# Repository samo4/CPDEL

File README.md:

# CPDEL

## Completely Pointless DC Electronic Load

> This a 2-channel DC electronic load, built from [cheap chinese DC load modbus modules](./firmware/SOUSIM.md).

Features:

- 2 channels: 200V, 10A
- 4 modes (CC, CV, CR, CP) + battery discharge mode
- Control:
  - 2.8" SPI display with capacitive touch
  - telnet SCPI interface (port 5025)
  - REST SCPI interface (port 80)
  - responsive web interface (with sockets)
- rudimentary charting
- OTA updates with CI/CD integration
- not-unreasonable level of test coverage
- UDP logging for debugging

## Development

You need a working installation of Python 3.x, [ESP-IDF v6.x](https://docs.espressif.com/projects/esp-idf/en/stable/esp32/get-started/windows-setup.html) and a working C compiler (the Xtensa one and a native for your host system - tested only with Visual studio build system). Use vscode to open the firmware folder, which contains the `.vscode` settings, including the most important: initialization of ESP-IDF terminal.

In ESP-IDF terminal (folder `firmware/esp`) you can then run `./esp.ps1`

## Key takeaways

- don't use http servers for OTA that you don't fully control, because you have no control over TLS chain.. updates to chain can break your OTA
- don't use SPI display if you want full screen animations, it's too slow
- don't use single pole switches for mains...
- keep LVGL memory as low as possible, to crash early when we have a leak?

## LLM disclaimer

Hardware and first few versions of software were created the old fashined way. It worked, but only the exact features that I needed at the time. With the help of LLM, the code was rewritten to use ESP-IDF (compared to original Arduino FreeRTOSnstein) directly and implement basicly all of the features that one might expect from a DC load instrument. LLM was used heavily especially in the UI, http/ws/socket server code and test writing.

"Copilot Is For Entertainment Purposes Only" is written in the Copilot terms. Well, I was entertained.

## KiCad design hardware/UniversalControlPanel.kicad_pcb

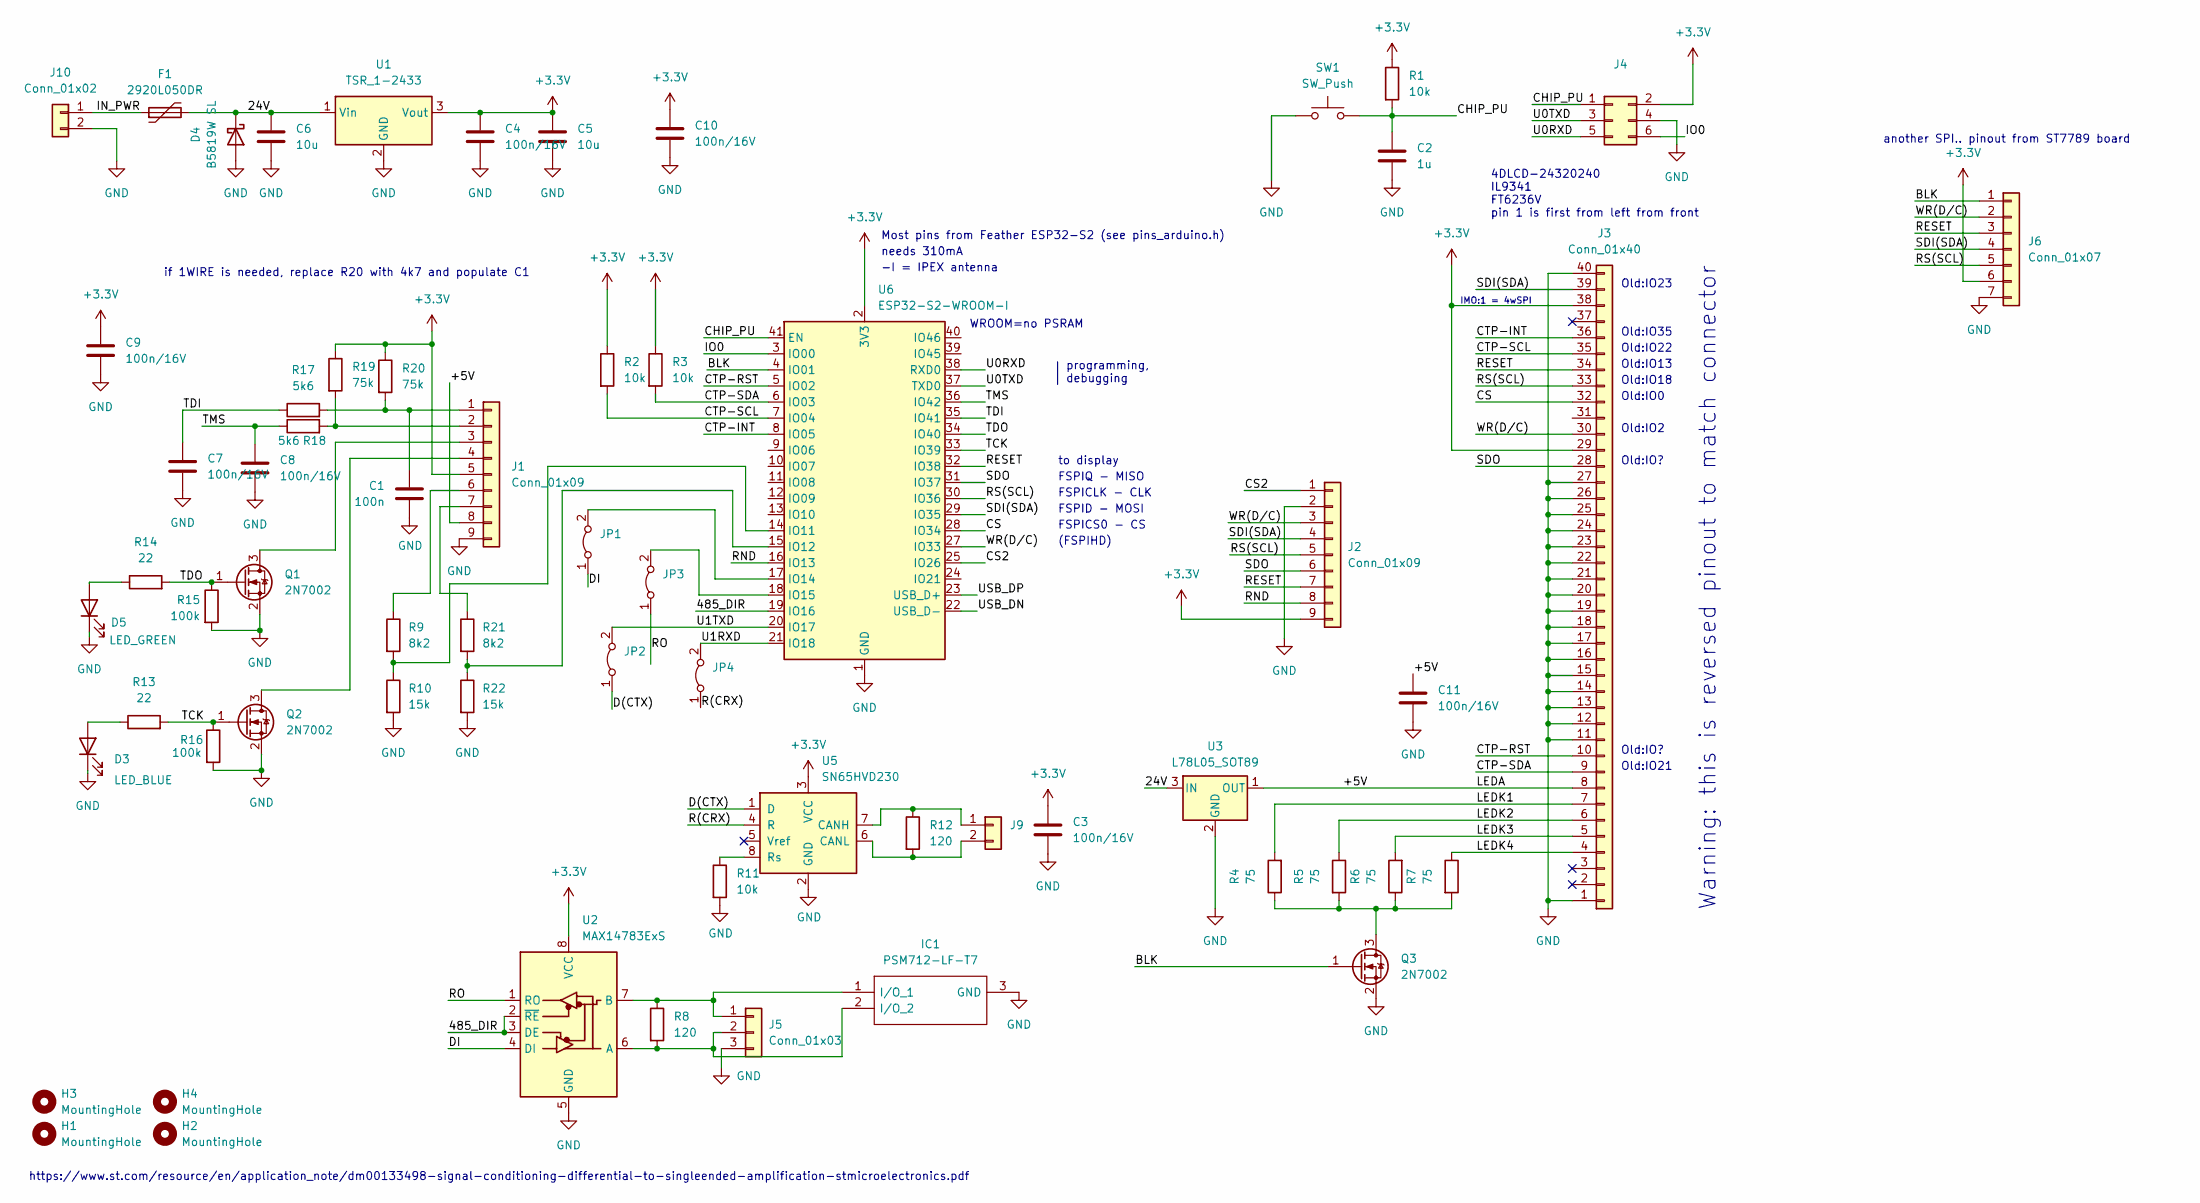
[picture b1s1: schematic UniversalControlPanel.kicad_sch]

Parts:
C1: 100n; C_0402_1005Metric; LCSC C1525
C2: 1u; C_0402_1005Metric
C3, C4, C7, C8, C9, C10, C11: 100n/16V; C_0402_1005Metric; LCSC C1525
C5, C6: 10u; C_1206_3216Metric; LCSC C13585
D3: LED_BLUE; LED_0603_1608Metric; LCSC C72041
D4: B5819W SL; D_SOD-123; LCSC C8598
D5: LED_GREEN; LED_0603_1608Metric; LCSC C72043
F1: 2920L050DR; Fuse_2920_7451Metric; Mouser Part Number 576-2920L050
H1, H2, H3, H4: MountingHole; MountingHole_3.5mm
IC1: PSM712-LF-T7; SOT-23; Manufacturer_Part_Number PSM712-LF-T7; LCSC C32677
J1: Conn_01x09; JST_XH_B9B-XH-A_1x09_P2.50mm_Vertical
J2: Conn_01x09; PinHeader_1x09_P2.54mm_Vertical
J3: Conn_01x40; Hirose_FH12-40S-0.5SH_1x40-1MP_P0.50mm_Horizontal; LCSC C506795
J4: Conn_02x03_Odd_Even; PinHeader_2x03_P2.54mm_Vertical
J5: Conn_01x03; JST_XH_B3B-XH-A_1x03_P2.50mm_Vertical
J6: Conn_01x07; PinHeader_1x07_P2.54mm_Vertical
J9: Conn_01x02; JST_XH_B2B-XH-A_1x02_P2.50mm_Vertical
J10: Conn_01x02; 1985807
JP1, JP2, JP3, JP4: Jumper_2_Bridged; SolderJumper-2_P1.3mm_Bridged2Bar_RoundedPad1.0x1.5mm
Q1, Q2, Q3: 2N7002; SOT-23; LCSC C8545
R1, R2, R3, R11: 10k; R_0402_1005Metric; LCSC C25744
R4, R5, R6, R7: 75; R_0402_1005Metric; LCSC C25133
R8, R12: 120; R_0805_2012Metric_Pad1.20x1.40mm_HandSolder
R9, R21: 8k2; R_0402_1005Metric; LCSC C25924
R10, R22: 15k; R_0402_1005Metric; LCSC C25756
R13, R14: 22; R_0402_1005Metric
R15, R16: 100k; R_0402_1005Metric
R17, R18: 5k6; R_0402_1005Metric; LCSC C25908
R19, R20: 75k; R_0402_1005Metric; LCSC C25798
SW1: SW_Push; TS-1187A-B-A-B; LCSC C318884
U1: TSR_1-2433; Converter_DCDC_TRACO_TSR-1_THT
U2: MAX14783ExS; SOIC-8_3.9x4.9mm_P1.27mm; LCSC C559550
U3: L78L05_SOT89; SOT-89-3
U5: SN65HVD230; SOIC-8_3.9x4.9mm_P1.27mm
U6: ESP32-S2-WROOM-I; ESP32-S2-WROVER; LCSC C967026

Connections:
+3V3: C3.1, C4.1, C5.1, C9.1, C10.1, J1.5, J2.9, J3.29, J3.38, J4.2, J6.6, R1.1, R2.1, R3.1, R19.1, R20.1, U1.3 (Vout), U2.8 (VCC), U5.3 (VCC), U6.2 (3V3)
/24V: C6.1, D4.1 (K), F1.2, U1.1 (Vin), U3.3 (IN)
/485_DIR: U2.2 (~RE), U2.3 (DE), U6.19 (IO16)
/+5V: C11.1, J1.8, J3.8, U3.1 (OUT)
/BLK: J6.1, Q3.1 (G), U6.4 (IO01)
/CHIP_PU: C2.1, J4.1, R1.2, SW1.2, U6.41 (EN)
/CS: J3.32, U6.28 (IO34)
/CS2: J2.1, U6.25 (IO26)
/CTP-INT: J3.36, U6.8 (IO05)
/CTP-RST: J3.10, U6.5 (IO02)
/CTP-SCL: J3.35, R2.2, U6.7 (IO04)
/CTP-SDA: J3.9, R3.2, U6.6 (IO03)
/D(CTX): JP2.1 (A), U5.1 (D)
/DI: JP1.1 (A), U2.4 (DI)
/IN_PWR: F1.1, J10.1
/IO0: J4.6, U6.3 (IO00)
/LEDK1: J3.7, R4.2
/LEDK2: J3.6, R5.1
/LEDK3: J3.5, R6.2
/LEDK4: J3.4, R7.1
/R(CRX): JP4.1 (A), U5.4 (R)
/RESET: J2.7, J3.34, J6.3, U6.32 (IO38)
/RND: J2.8, U6.16 (IO13)
/RO: JP3.1 (A), U2.1 (RO)
/RS(SCL): J2.5, J3.33, J6.5, U6.30 (IO36)
/SDI(SDA): J2.4, J3.39, J6.4, U6.29 (IO35)
/SDO: J2.6, J3.28, U6.31 (IO37)
/TCK: Q2.1 (G), R13.2, R16.1, U6.33 (IO39)
/TDI: C7.1, R17.1, U6.35 (IO41)
/TDO: Q1.1 (G), R14.2, R15.1, U6.34 (IO40)
/TMS: C8.1, R18.1, U6.36 (IO42)
/U0RXD: J4.5, U6.38 (RXD0)
/U0TXD: J4.3, U6.37 (TXD0)
/U1RXD: JP4.2 (B), U6.21 (IO18)
/U1TXD: JP2.2 (B), U6.20 (IO17)
/USB_DN: U6.22 (USB_D-)
/USB_DP: U6.23 (USB_D+)
/WR(D/C): J2.3, J3.30, J6.2, U6.27 (IO33)
GND: C1.1, C2.2, C3.2, C4.2, C5.2, C6.2, C7.2, C8.2, C9.2, C10.2, C11.2, D3.1 (K), D4.2 (A), D5.1 (K), IC1.3 (GND), J1.9, J2.2, J3.1, J3.11, J3.12, J3.13, J3.14, J3.15, J3.16, J3.17, J3.18, J3.19, J3.20, J3.21, J3.22, J3.23, J3.24, J3.25, J3.26, J3.27, J3.40, J4.4, J5.3, J6.7, J10.2, Q1.2 (S), Q2.2 (S), Q3.2 (S), R10.2, R11.2, R15.2, R16.2, R22.2, SW1.1, U1.2 (GND), U2.5 (GND), U3.2 (GND), U5.2 (GND), U6.1 (GND), U6.26 (GND), U6.42 (GND), U6.43 (GND)
unnamed: C1.2, J1.1, R17.2, R20.2
unnamed: D3.2 (A), R13.1
unnamed: D5.2 (A), R14.1
unnamed: IC1.1 (I/O_1), J5.1, R8.1, U2.7 (B)
unnamed: IC1.2 (I/O_2), J5.2, R8.2, U2.6 (A)
unnamed: J1.2, R18.2, R19.2
unnamed: J1.3, Q1.3 (D)
unnamed: J1.4, Q2.3 (D)
unnamed: J1.6, R9.1
unnamed: J1.7, R21.1
unnamed: J9.1, R12.1, U5.7 (CANH)
unnamed: J9.2, R12.2, U5.6 (CANL)
unnamed: JP1.2 (B), U6.17 (IO14)
unnamed: JP3.2 (B), U6.18 (IO15)
unnamed: Q3.3 (D), R4.1, R5.2, R6.1, R7.2
unnamed: R9.2, R10.1, U6.14 (IO11)
unnamed: R11.1, U5.8 (Rs)
unnamed: R21.2, R22.1, U6.15 (IO12)

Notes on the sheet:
Old:IO35
Most pins from Feather ESP32-S2 (see pins_arduino.h)
Old:IO?
FSPICS0 - CS
Old:IO13
Old:IO23
WROOM=no PSRAM
(FSPIHD)
Warning: this is reversed pinout to match connector
-I = IPEX antenna
if 1WIRE is needed, replace R20 with 4k7 and populate C1
https://www.st.com/resource/en/application_note/dm00133498-signal-conditioning-differential-to-singleended-amplification-stmicroelectronics.pdf
Old:IO2
to display
IMO:1 = 4wSPI
FSPICLK - CLK
Old:IO22
Old:IO21
4DLCD-24320240 IL9341 FT6236V pin 1 is first from left from front
another SPI.. pinout from ST7789 board
FSPID - MOSI
FSPIQ - MISO
Old:IO18
needs 310mA
Old:IO0
programming, debugging

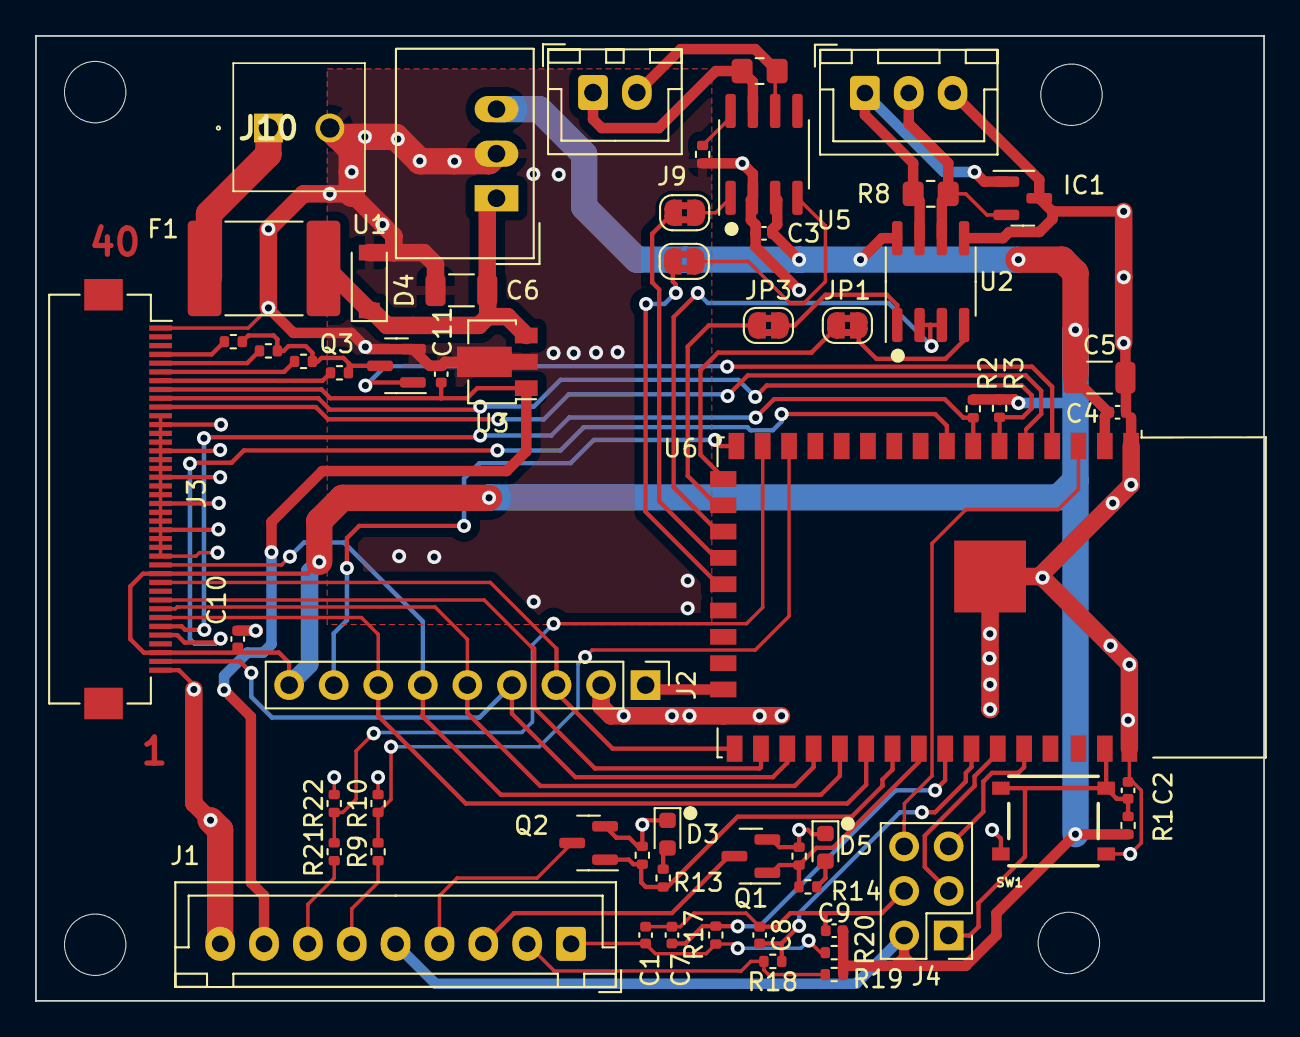
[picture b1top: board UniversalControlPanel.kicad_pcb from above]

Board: 2 copper layers, 70.0 x 55.0 mm, 62 parts (0 on the bottom side), 55 nets.

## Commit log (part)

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2022-01-02 initial
2022-01-02 components
2022-01-03 pcb first place
2022-01-03 removed autosave
2022-01-03 moved input sch
2022-01-03 some changes
2022-01-05 replaced with TSR
2022-01-05 hirose
2022-01-05 random additions
2022-01-06 finalizing features
2022-01-07 connector finalized
2022-01-07 placed
2022-01-09 movin st7789
2022-01-09 added switch
2022-07-24 restart work
2022-07-24 wired
2022-07-25 before reversing display
2022-07-25 before upload
2022-07-25 went to production
2023-03-05 joining
2024-10-26 failed experiment
2024-10-26 ipv6 says hello
2024-10-26 failing http ivp6
2024-10-27 panda
2024-11-03 ping package
2025-05-18 empty project
2025-05-18 more default
2025-05-18 default lv_conf
2025-05-18 my lv_conf
2025-05-18 old lv_conf
2025-05-20 why this compiles?
2025-05-27 smth
2026-03-20 playing
2026-03-20 compiles
2026-03-20 it's something
2026-03-21 nice numpad
2026-03-21 worky
2026-03-21 first graph
2026-03-21 wireless mockup
2026-03-21 less rounded corners
2026-03-21 wifi config
2026-03-22 esp ifdef
2026-03-22 more reliable cmake
2026-03-22 stack checking and null ptr
2026-03-22 defensive prog
2026-03-22 split folders
2026-03-22 tidy
2026-03-22 esp ignore
2026-03-22 lv_conf_common
2026-03-22 esp builds
2026-03-22 safe
2026-03-22 display no-worky
2026-03-22 ILI9341 build. works? who knows
2026-03-22 moved mains
2026-03-22 ready for OTA
2026-03-23 spi works
2026-03-23 ili9341_init_from_datasheet
2026-03-23 works
2026-03-23 straightforward build script
2026-03-24 touch in progress
2026-03-25 touch works
2026-03-25 faster link
2026-03-25 wifi works
2026-03-25 web server
2026-03-25 readme
2026-03-27 no anim, ch count, modal panel
2026-03-27 lv_obj_is_valid is not need if no free; no anim
2026-03-27 ch count
2026-03-27 ch count & is valid not needed
2026-03-27 add access to ssid/pass
2026-03-27 now with keyboard
2026-03-27 no more panice
2026-03-27 modbus wip
2026-03-27 going the queue dir
2026-03-28 already cute
2026-03-28 now with low_voltage_cutoff
2026-03-28 colors
2026-03-28 now with a nice unified struct for bus
2026-03-28 rename
2026-03-28 wrapping renaming
2026-03-28 hahahah
2026-03-28 Fix ESP-IDF setup and build steps
2026-03-28 Remove pkg_resources check in OTA workflow
2026-03-28 Fix CI app binary detection for ESP-IDF build output
2026-03-28 Simplify firmware binary detection (remove inline Python)
2026-03-28 OTA missing file
2026-03-29 ota ok
2026-03-29 modal, unused timer and ui_log
2026-03-29 ui_modal
2026-03-29 ui_log
2026-03-29 stack search
2026-03-29 are we there yet, papa smurf?
2026-03-29 lazy is still static - no benefit
2026-03-29 de-em-dash and surge
2026-03-29 with some info
2026-03-29 doc cleanup
2026-03-29 add graph
2026-03-29 add note
2026-03-29 clena
2026-03-29 add documentation
2026-03-29 removing old files
2026-03-29 testž
2026-03-29 moving
2026-04-04 back to 80Mhz
2026-04-05 reduce to idle; prevent multiple cmds on bus
2026-04-05 prevent jumping to conclusions
2026-04-05 v0.1
2026-04-05 fixing build
2026-04-05 esp-wifi-logger inspired simple UDP logger
2026-04-05 comment
2026-04-05 v0.2
2026-04-05 v0.3
2026-04-05 v0.4
2026-04-05 knowhow
2026-04-05 v0.5
2026-04-05 v0.6
2026-04-05 ignore
2026-04-05 v0.7
2026-04-05 v0.8
2026-04-05 UDP_LOG_SYSLOG
2026-04-05 ui_touch_debug
2026-04-05 note
2026-04-05 more area to click channel
2026-04-06 better touch experience
2026-04-06 better touch debug
2026-04-06 numpad and keyboard now on demand (to reduce memory)
2026-04-06 random refactoring
2026-04-06 I like my enums
2026-04-06 add tests
2026-04-06 rename queue
2026-04-06 keep it similar to others
2026-04-06 moving DC_LOAD_DEVICE_COUNT
2026-04-06 let's use less RAM
2026-04-06 ota dynamic load screen
2026-04-06 cleanup
2026-04-06 don't think we need these
2026-04-06 better malloc_failed_cb
2026-04-06 remove power, add APP_CMD_SOUR_
2026-04-06 prevent bad scanf
2026-04-06 working scpi_server
2026-04-06 v0.9
2026-04-06 v0.10
2026-04-06 v0.11
2026-04-06 todo
2026-04-06 notes
2026-04-06 refactor to single queue with reply-to
2026-04-07 tests all good
2026-04-10 playing with stack and hwm
2026-04-10 www and ws tests
2026-04-10 hwm unification and reduce max_sockets
2026-04-10 rtrim
2026-04-10 v0.12
2026-04-10 v0.13
2026-04-11 v0.14
2026-04-11 rnd clean
2026-04-11 v0.15
2026-04-11 typo
2026-04-11 v0.16
2026-04-11 v0.17
2026-04-11 ota crash fix
2026-04-11 docs
2026-04-11 v0.19
2026-04-11 don't deploy stale versions
2026-04-11 v0.20
2026-04-11 add features
2026-06-18 report
2026-06-18 spellcheck
2026-06-19 date
2026-06-22 fix sim because of all the changes in development
2026-06-22 prevent inf loop
2026-06-22 fix cast problem
